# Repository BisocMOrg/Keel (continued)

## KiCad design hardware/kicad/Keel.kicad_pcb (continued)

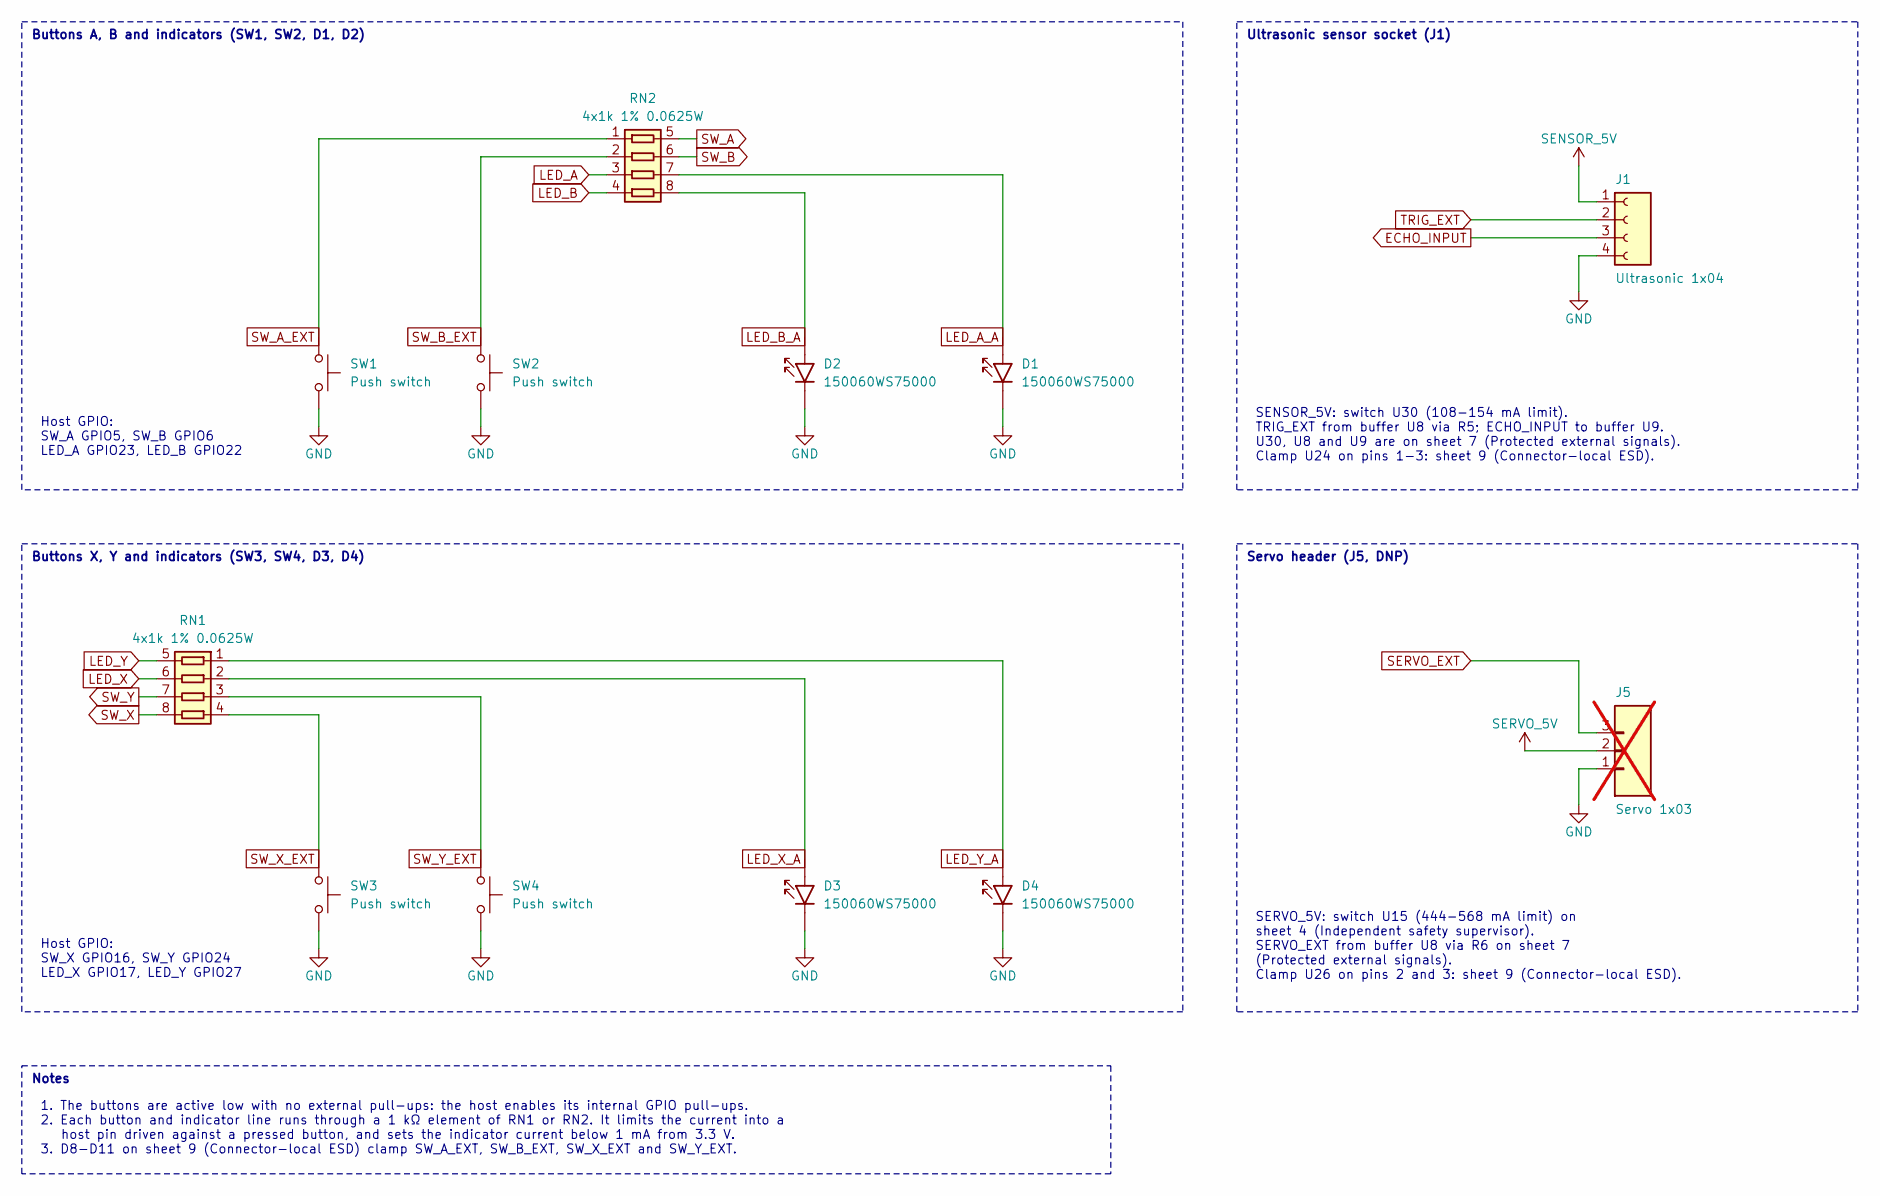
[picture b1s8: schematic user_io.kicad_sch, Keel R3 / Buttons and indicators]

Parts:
D1, D2, D3, D4: 150060WS75000; LED_0603_1608Metric; MPN 150060WS75000
J1: Ultrasonic 1x04; PinSocket_1x04_P2.54mm_Vertical; MPN SSW-104-01-G-S
J5: Servo 1x03; PinHeader_1x03_P2.54mm_Vertical; not fitted
RN1, RN2: 4x1k 1% 0.0625W; YC164_4x0603; MPN YC164-FR-071KL
SW1, SW2, SW3, SW4: Push switch; SW_SPST_PTS645Sx43SMTR92; MPN PTS645SM43SMTR92

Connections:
ECHO_INPUT: J1.3; also elsewhere on the board
GND: D1.1 (K), D2.1 (K), D3.1 (K), D4.1 (K), J1.4, J5.1, SW1.2 (ground), SW2.2 (ground), SW3.2 (ground), SW4.2 (ground); also elsewhere on the board
LED_A: RN2.3; also elsewhere on the board
LED_A_A: D1.2 (A), RN2.7
LED_B: RN2.4; also elsewhere on the board
LED_B_A: D2.2 (A), RN2.8
LED_X: RN1.6; also elsewhere on the board
LED_X_A: D3.2 (A), RN1.2
LED_Y: RN1.5; also elsewhere on the board
LED_Y_A: D4.2 (A), RN1.1
SENSOR_5V: J1.1; also elsewhere on the board
SERVO_5V: J5.2; also elsewhere on the board
SERVO_EXT: J5.3; also elsewhere on the board
SW_A: RN2.5; also elsewhere on the board
SW_A_EXT: RN2.1, SW1.1 (contact); also elsewhere on the board
SW_B: RN2.6; also elsewhere on the board
SW_B_EXT: RN2.2, SW2.1 (contact); also elsewhere on the board
SW_X: RN1.8; also elsewhere on the board
SW_X_EXT: RN1.4, SW3.1 (contact); also elsewhere on the board
SW_Y: RN1.7; also elsewhere on the board
SW_Y_EXT: RN1.3, SW4.1 (contact); also elsewhere on the board
TRIG_EXT: J1.2; also elsewhere on the board

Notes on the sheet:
Buttons A, B and indicators (SW1, SW2, D1, D2)
Buttons X, Y and indicators (SW3, SW4, D3, D4)
Ultrasonic sensor socket (J1)
Servo header (J5, DNP)
Host GPIO: SW_A GPIO5, SW_B GPIO6 LED_A GPIO23, LED_B GPIO22
Host GPIO: SW_X GPIO16, SW_Y GPIO24 LED_X GPIO17, LED_Y GPIO27
SENSOR_5V: switch U30 (108-154 mA limit). TRIG_EXT from buffer U8 via R5; ECHO_INPUT to buffer U9. U30, U8 and U9 are on sheet 7 (Protected external signals). Clamp U24 on pins 1-3: sheet 9 (Connector-local ESD).
SERVO_5V: switch U15 (444-568 mA limit) on sheet 4 (Independent safety supervisor). SERVO_EXT from buffer U8 via R6 on sheet 7 (Protected external signals). Clamp U26 on pins 2 and 3: sheet 9 (Connector-local ESD).
Notes
1. The buttons are active low with no external pull-ups: the host enables its internal GPIO pull-ups. 2. Each button and indicator line runs through a 1 kΩ element of RN1 or RN2. It limits the current into a host pin driven against a pressed button, and sets the indicator current below 1 mA from 3.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

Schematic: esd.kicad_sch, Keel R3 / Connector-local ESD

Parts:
D8, D9, D10, D11: TPD1E05U06DYAR; TI_DYA0002A_TPD1E05U06_SOD523; MPN TPD1E05U06DYAR
U17, U18, U19, U20, U21, U22, U23, U24, U25, U26: TPD4E05U06DQAR; TI_DQA0010A_TPD4E05U06_AB_Compatible_CommonMask; MPN TPD4E05U06DQAR

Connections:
ECHO_INPUT: U24.4 (IO4); also elsewhere on the board
EXP_3V3: U17.1 (IO1), U18.1 (IO1), U19.1 (IO1), U20.1 (IO1), U21.1 (IO1), U22.1 (IO1), U23.1 (IO1), U25.1 (IO1); also elsewhere on the board
EXP_I2C_SCL: U17.4 (IO4), U18.4 (IO4), U19.4 (IO4), U20.4 (IO4), U21.4 (IO4), U22.4 (IO4), U23.4 (IO4), U25.4 (IO4); also elsewhere on the board
EXP_I2C_SDA: U17.2 (IO2), U18.2 (IO2), U19.2 (IO2), U20.2 (IO2), U21.2 (IO2), U22.2 (IO2), U23.2 (IO2), U25.2 (IO2); also elsewhere on the board
EXP_INT_INPUT: U17.5 (IO5), U18.5 (IO5), U19.5 (IO5), U20.5 (IO5), U21.5 (IO5), U25.5 (IO5); also elsewhere on the board
GND: D8.2 (GND), D9.2 (GND), D10.2 (GND), D11.2 (GND), U17.3 (GND), U17.8 (GND), U18.3 (GND), U18.8 (GND), U19.3 (GND), U19.8 (GND), U20.3 (GND), U20.8 (GND), U21.3 (GND), U21.8 (GND), U22.3 (GND), U22.8 (GND), U23.3 (GND), U23.8 (GND), U24.3 (GND), U24.8 (GND), U25.3 (GND), U25.8 (GND), U26.3 (GND), U26.8 (GND); also elsewhere on the board
SENSOR_5V: U24.1 (IO1); also elsewhere on the board
SERVO_5V: U26.1 (IO1); also elsewhere on the board
SERVO_EXT: U26.2 (IO2); also elsewhere on the board
SW_A_EXT: D8.1 (IO1); also elsewhere on the board
SW_B_EXT: D9.1 (IO1); also elsewhere on the board
SW_X_EXT: D10.1 (IO1); also elsewhere on the board
SW_Y_EXT: D11.1 (IO1); also elsewhere on the board
TRIG_EXT: U24.2 (IO2); also elsewhere on the board

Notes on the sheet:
Protects JP1
Protects JP2
Protects JP3
Protects JP4
Protects JP5
Expansion header clamps (U17-U21)
Protects J4
Protects X1
Protects X3
J4 and I2C socket clamps (U25, U22, U23)
Protects J1
Ultrasonic sensor socket clamp (U24)
Protects J5
Servo header clamp (U26)
Protects SW1
Protects SW2
Protects SW3
Protects SW4
Push-button clamps (D8-D11)
Notes
1. Each clamp sits beside the connector or switch it protects, with a short, direct return to GND. 2. IO1 of each array clamps the connector supply pin (EXP_3V3, SENSOR_5V or SERVO_5V). 3. The clamps absorb ESD transients only. Sustained faults are handled downstream by the series resistors, curren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

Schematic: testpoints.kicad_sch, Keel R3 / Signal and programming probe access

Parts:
TP1: PI_5V; TestPoint_Pad_D1.5mm; MPN BARE PCB PAD - NO FITTED PART
TP2: SYS_5V; TestPoint_Pad_D1.5mm; MPN BARE PCB PAD - NO FITTED PART
TP3: VM_MOTOR; TestPoint_Pad_D1.5mm; MPN BARE PCB PAD - NO FITTED PART
TP4: PI_3V3; TestPoint_Pad_D1.5mm; MPN BARE PCB PAD - NO FITTED PART
TP5: EXP_3V3; TestPoint_Pad_D1.5mm; MPN BARE PCB PAD - NO FITTED PART
TP6, TP40: GND; TestPoint_Pad_D1.5mm; MPN BARE PCB PAD - NO FITTED PART
TP7: I2C_SDA; TestPoint_Pad_D1.5mm; MPN BARE PCB PAD - NO FITTED PART
TP8: I2C_SCL; TestPoint_Pad_D1.5mm; MPN BARE PCB PAD - NO FITTED PART
TP9: MOTOR_EN; TestPoint_Pad_D1.5mm; MPN BARE PCB PAD - NO FITTED PART
TP10: MOTOR_FAULT; TestPoint_Pad_D1.5mm; MPN BARE PCB PAD - NO FITTED PART
TP12: MOTOR_ISEN_A; TestPoint_Pad_D1.5mm; MPN BARE PCB PAD - NO FITTED PART
TP13: MOTOR_ISEN_B; TestPoint_Pad_D1.5mm; MPN BARE PCB PAD - NO FITTED PART
TP18: EXP_I2C_SDA; TestPoint_Pad_D1.5mm; MPN BARE PCB PAD - NO FITTED PART
TP19: EXP_I2C_SCL; TestPoint_Pad_D1.5mm; MPN BARE PCB PAD - NO FITTED PART
TP20: I2C_OVP_REF; TestPoint_Pad_D1.5mm; MPN BARE PCB PAD - NO FITTED PART
TP21: HOST_ARMED; TestPoint_Pad_D1.5mm; MPN BARE PCB PAD - NO FITTED PART
TP39: SAFE_3V3; TestPoint_Pad_D1.5mm; MPN BARE PCB PAD - NO FITTED PART
TP41: SAFETY_NRST; TestPoint_Pad_D1.5mm; MPN BARE PCB PAD - NO FITTED PART
TP42: SAFETY_SWDIO; TestPoint_Pad_D1.5mm; MPN BARE PCB PAD - NO FITTED PART
TP43: SAFETY_SWCLK; TestPoint_Pad_D1.5mm; MPN BARE PCB PAD - NO FITTED PART
TP44: MCU_WD_SERVICE; TestPoint_Pad_D1.5mm; MPN BARE PCB PAD - NO FITTED PART
TP45: SERVO_5V; TestPoint_Pad_D1.5mm; MPN BARE PCB PAD - NO FITTED PART
TP46: SERVO_POWER_EN; TestPoint_Pad_D1.5mm; MPN BARE PCB PAD - NO FITTED PART

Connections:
EXP_3V3: TP5.1 (1_1); also elsewhere on the board
EXP_I2C_SCL: TP19.1 (1_1); also elsewhere on the board
EXP_I2C_SDA: TP18.1 (1_1); also elsewhere on the board
GND: TP6.1 (1_1), TP40.1 (1_1); also elsewhere on the board
HOST_ARMED: TP21.1 (1_1); also elsewhere on the board
I2C_OVP_REF: TP20.1 (1_1); also elsewhere on the board
I2C_SCL: TP8.1 (1_1); also elsewhere on the board
I2C_SDA: TP7.1 (1_1); also elsewhere on the board
MCU_WD_SERVICE: TP44.1 (1_1); also elsewhere on the board
MOTOR_EN: TP9.1 (1_1); also elsewhere on the board
MOTOR_FAULT: TP10.1 (1_1); also elsewhere on the board
MOTOR_ISEN_A: TP12.1 (1_1); also elsewhere on the board
MOTOR_ISEN_B: TP13.1 (1_1); also elsewhere on the board
PI_3V3: TP4.1 (1_1); also elsewhere on the board
PI_5V: TP1.1 (1_1); also elsewhere on the board
SAFETY_NRST: TP41.1 (1_1); also elsewhere on the board
SAFETY_SWCLK: TP43.1 (1_1); also elsewhere on the board
SAFETY_SWDIO: TP42.1 (1_1); also elsewhere on the board
SAFE_3V3: TP39.1 (1_1); also elsewhere on the board
SERVO_5V: TP45.1 (1_1); also elsewhere on the board
SERVO_POWER_EN: TP46.1 (1_1); also elsewhere on the board
SYS_5V: TP2.1 (1_1); also elsewhere on the board
VM_MOTOR: TP3.1 (1_1); also elsewhere on the board

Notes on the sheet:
Pos
Net
Ref
Silkscreen
Expected reading
2 SYS5V
Within 60 mV of TP1 with U2 on; 0 V after a trip
6 GND
Row ground return
1 PI5V
5.0-5.1 V; below 5.2 V (U2 OVP trip 5.28 V min)
POWER row
13 ISB
Left motor shunt R36; chops at 180-230 mV
12 ISA
Right motor shunt R35; chops at 180-230 mV
GND
TP25
25 GND
Row ground return, sheet 11 (Local probe ground returns)
3 VM
TP2 minus the D5 drop (0.3-0.4 V while driving)
MOTOR row
45 S5V
5 V only during a servo burst (500 ms max)
TP47
47 GND
SERVO row
39 3V3S
3.234-3.366 V; probe VTref only, never feed
40 GND
41 RST
U12 NRST; held LOW while MOTOR_FAULT is LOW
43 CLK
SWD clock, U12 PA14-BOOT0
42 DIO
SWD data, U12 PA13
Set SW5 to PROG (all ON) before attaching an SWD probe.
SWD row
44 WDI

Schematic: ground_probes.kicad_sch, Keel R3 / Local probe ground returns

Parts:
TP24, TP25, TP26, TP47: GND; TestPoint_Pad_D1.5mm; MPN BARE PCB PAD - NO FITTED PART

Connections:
GND: TP24.1 (1_1), TP25.1 (1_1), TP26.1 (1_1), TP47.1 (1_1); also elsewhere on the board

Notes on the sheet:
Row
Pos
Net
Ref
Silkscreen
Ground return for
MOTOR
25 GND
TP13, TP12, TP3
SERVO
47 GND
TP45
STATUS
26 GND
TP44, TP4, TP10, TP21, TP9, TP46
I2C
24 GND
TP7, TP8, TP18, TP19, TP20, TP5
Row GND pads
Notes
1. Bare 1.5 mm ENIG pads on the bottom side, without paste or a fitted part; they are not in the BOM. 2. Each pad sits in its probe row on the 2.54 mm grid, beside the row signals, for a short return loop. 3. Pos counts along the row from its silkscreen label (west to east in top view), as on sheet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

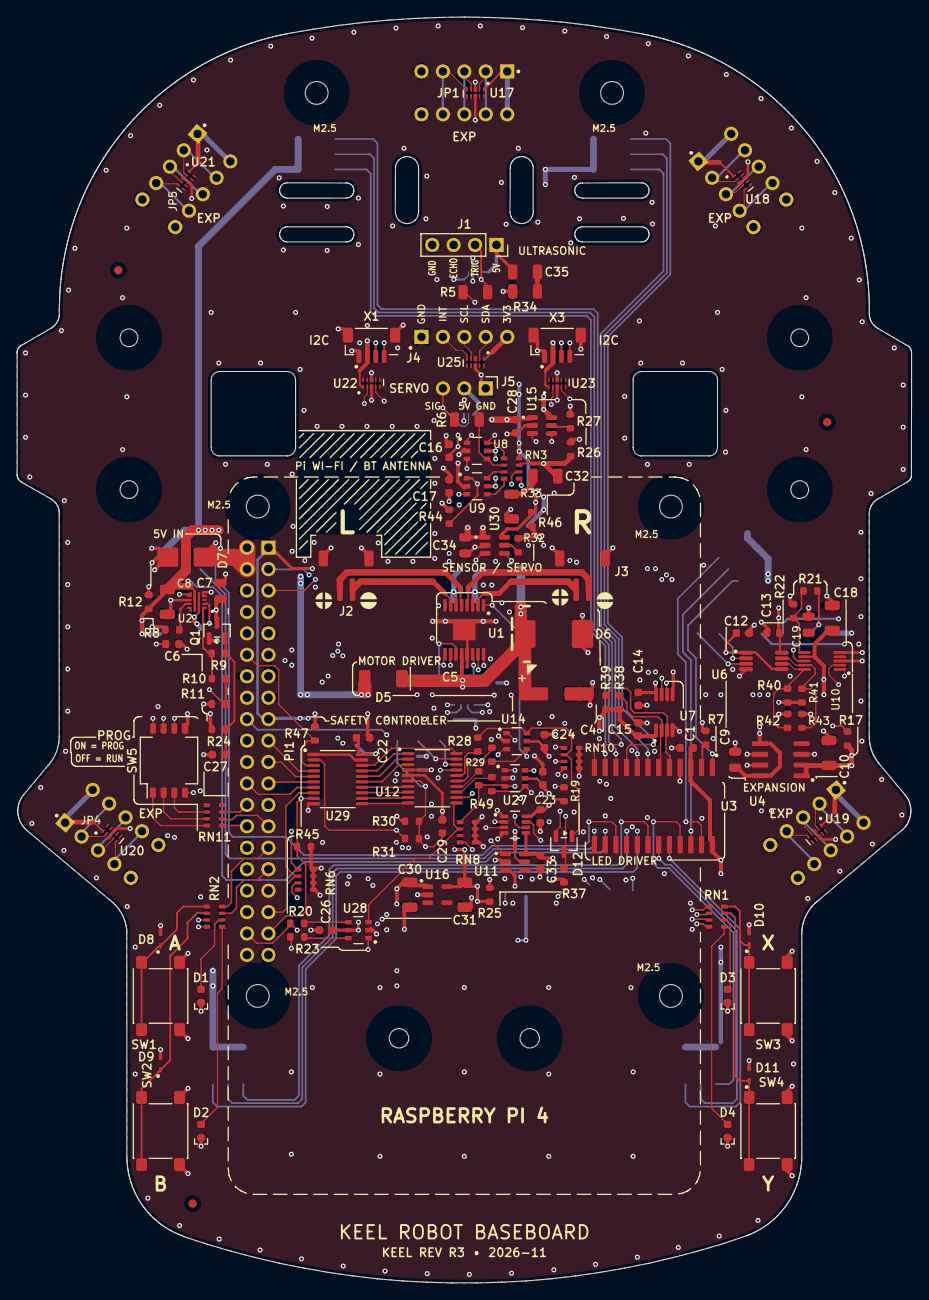
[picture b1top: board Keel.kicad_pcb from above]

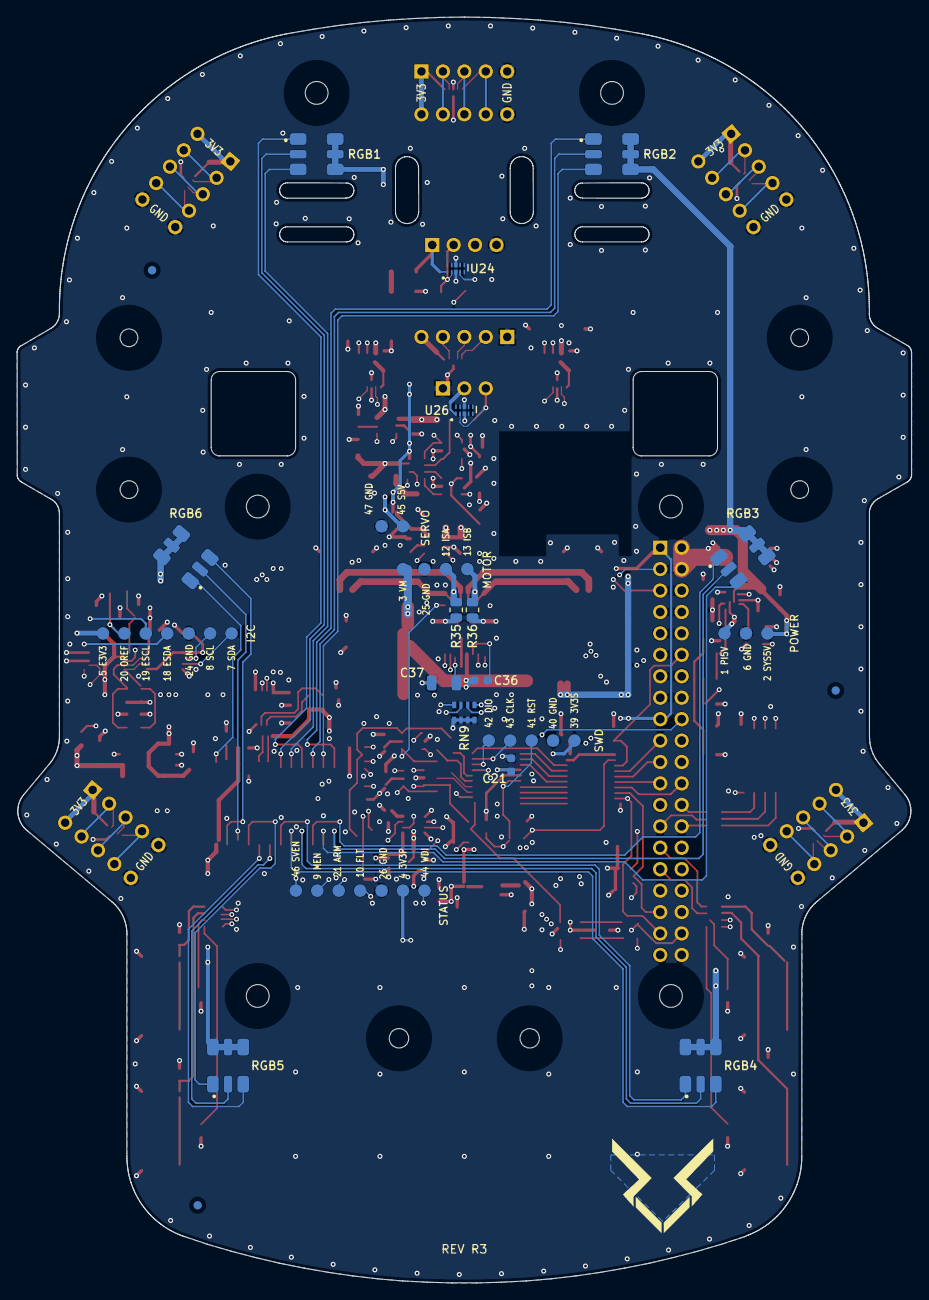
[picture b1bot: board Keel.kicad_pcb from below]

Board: 6 copper layers, 106.0 x 150.0 mm, 193 parts (45 on the bottom side), 124 nets.

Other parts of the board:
FID1, FID2, FID3, FID4, FID5, FID6: Fiducial; Fiducial_1mm_Mask2mm
H1, H2: MountingHole_2.3mm_NPTH
H3, H5: MountingHole_2.7mm_NPTH_PiHeaderClip
H4, H6, H11, H12: MountingHole_2.7mm_NPTH
H7, H8, H9, H10: MountingHole_2.1mm_NPTH

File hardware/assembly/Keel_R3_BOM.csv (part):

Item,Qty per board,Designators,Manufacturer,Manufacturer Part Number,Description,Value,Package,Mounting,Side,Approved alternates,Notes,Footprint (CPL)
1,1,PI1,Samtec,SSW-120-01-G-D,"Socket strip, female, 2x20, 2.54 mm pitch, vertical, through-hole, gold, lead style -01 (Raspberry Pi 40-pin)",2x20 female socket,"THT 2x20, 2.54 mm",THT,Top,,"exact part only - no substitution; THT, not in the CPL: hand-solder after reflow, no wave soldering (selective soldering only by prior agreement); seat flush and square; lead style -01 (tail length) required",PinSocket_2x20_P2.54mm_Vertical
2,1,U1,Texas Instruments,DRV8411PWPR,"Dual H-bridge motor driver, 1.65-11 V, current regulation on external sense resistors",DRV8411PWPR,HTSSOP-16 PowerPAD (PWP),SMD,Top,"DRV8833PWPR (TI) - the ONLY accepted alternate; C36/C37 are fitted for it. NOT DRV8411APWPR, NOT any DRV8833 ""-HX"" clone",exact part only - no substitution (the listed alternate / packaging variant is approved); exposed PowerPAD must be soldered; X-ray first boards,DRV8411A_PWP0016_C01_ExternalVias
3,1,C4,Panasonic,EEE-FP1C470AP,"Aluminium electrolytic capacitor, 47 uF, 16 V, low ESR, SMD (FP series)",47uF 16V,SMD Al-electrolytic 6.3 x 5.8 mm,SMD,Top,,POLARIZED: + terminal on pad 1 (VM_MOTOR); 5.8 mm tall,CP_Elec_6.3x5.8
4,2,"J2,J3",JST,S2B-ZR-SM4A-TF(LF)(SN),"Connector header, JST ZH, 2-pos, 1.5 mm pitch, side entry, SMD, tin",JST ZH 2-pin,"SMD, 1x02 + 2 MP",SMD,Top,,engineering BOM code S2B-ZR-SM4A-TF,JST_ZH_S2B-ZR-SM4A-TF_1x02-1MP_P1.50mm_Horizontal
5,1,U3,Lumissil,IS31FL3218-GRLS2,"18-channel constant-current LED driver, I2C",IS31FL3218-GRLS2,SOP-24,SMD,Top,"IS31FL3218-GRLS2-TR (same part, tape and reel)",exact part only - no substitution (the listed alternate / packaging variant is approved),IS31FL3218_SOP24
6,16,"C1,C12,C13,C14,C15,C16,C17,C21,C22,C23,C24,C25,C26,C27,C28,C33",Murata,GRM188R72A104KA35D,"MLCC 100 nF, 100 V, X7R, +/-10%",100nF 100V X7R,0603 (1608 metric),SMD,Both,"packaging suffix only (Murata D<->J paper reel, L<->K embossed reel)","top: C1,C12,C13,C14,C15,C16,C17,C22,C23,C24,C25,C26,C27,C28,C33; bottom: C21",C_0603_1608Metric
7,1,R7,YAGEO,RC0603FR-0712KL,"Thick-film resistor 12 kohm, 1%, 0.1 W",12k 1%,0603 (1608 metric),SMD,Top,,,R_0603_1608Metric
8,6,"RGB1,RGB2,RGB3,RGB4,RGB5,RGB6",Inolux,IN-P55TATRGB,"RGB LED, top-view, 3 chips (R/G/B), PLCC-6",RGB LED,PLCC-6 5.0 x 5.5 mm,SMD,Bottom,,"BOTTOM side (top-view LED mounted on B, emits away from the board); pin 1 = silk dot / chamfered corner on sheet 2 of Keel_R3_assembly_drawing.pdf (pad 1 = blue cathode, pads 4-6 common anode); bottom CPL angles are KiCad-native (X not mirrored), so orient by that sheet",LED_Inolux_IN-P55TATRGB_PLCC6_5.0x5.5mm_P1.8mm
9,2,"X1,X3",JST,BM04B-SRSS-TB(LF)(SN),"Connector header, JST SH, 4-pos, 1.0 mm pitch, vertical (top entry), SMD, tin",I2C JST-SH 4P,"SMD, 1x04 + 2 MP",SMD,Top,,engineering BOM code BM04B-SRSS-TB,JST_SH_BM04B-SRSS-TB_1x04-1MP_P1.00mm_Vertical
10,1,J1,Samtec,SSW-104-01-G-S,"Socket strip, female, 1x4, 2.54 mm pitch, vertical, through-hole, gold, lead style -01 (HC-SR04)",1x4 female socket,"THT 1x4, 2.54 mm",THT,Top,,"exact part only - no substitution; THT, not in the CPL: hand-solder after reflow, no wave soldering (selective soldering only by prior agreement); seat flush and square",PinSocket_1x04_P2.54mm_Vertical
11,2,"R5,R6",YAGEO,RC1206FR-07330RL,"Thick-film resistor 330 ohm, 1%, 0.25 W",330R 1%,1206 (3216 metric),SMD,Top,,,R_1206_3216Metric
12,4,"RN1,RN2,RN3,RN11",YAGEO,YC164-FR-071KL,"Resistor array, 4 x 1 kohm, 1%, isolated, convex terminals",4x 1k 1%,YC164 array 3.2 x 1.6 mm (4x0603),SMD,Top,,,YC164_4x0603
13,4,"D1,D2,D3,D4",Wurth Elektronik,150060WS75000,"LED, white, 0603, water-clear, max. height 0.5 mm",LED white,0603 (1608 metric),SMD,Top,,"POLARITY: the body mark is the ANODE -> PCB pad 2 (LED_x_A), away from the silk cathode bracket; CPL angle already includes +180 deg",LED_0603_1608Metric
14,4,"SW1,SW2,SW3,SW4",C&K,PTS645SM43SMTR92 LFS,"Tactile switch, SPST-NO, 6 x 6 mm, 4.3 mm height, SMD gull-wing",Tactile switch,SMD 6 x 6 mm,SMD,Top,,engineering BOM code PTS645SM43SMTR92,SW_SPST_PTS645Sx43SMTR92
15,1,C5,Murata,GRM033R61E104KE14D,"MLCC 100 nF, 25 V, X5R, +/-10%",100nF 25V X5R,0201 (0603 metric),SMD,Top,"packaging suffix only (Murata D<->J paper reel, L<->K embossed reel)",0201 placed beside U1,C_0201_0603Metric
16,1,D5,Nexperia,PMEG6030ELPX,"Schottky rectifier, 60 V, 3 A",PMEG6030ELPX,SOD-128,SMD,Top,,"engineering BOM code PMEG6030ELP,115; POLARIZED: cathode band on pad 1 (VM_MOTOR)",D_SOD-128
17,1,D6,STMicroelectronics,SM15T6V8A,"TVS diode, UNIDIRECTIONAL, 1500 W, 5.8 V stand-off / 6.8 V breakdown",SM15T6V8A,SMC (DO-214AB),SMD,Top,,engineering BOM code SM15T6V8A-TR; UNIDIRECTIONAL (not SM15T6V8CA); cathode band on pad 1 (VM_MOTOR),D_SMC
18,7,"R12,R20,R23,R26,R28,R29,R31",YAGEO,RC0603FR-071KL,"Thick-film resistor 1 kohm, 1%, 0.1 W",1k 1%,0603 (1608 metric),SMD,Top,,,R_0603_1608Metric
19,1,U2,Texas Instruments,TPS259474LRPWR,"eFuse / protected load switch, 2.7-23 V, 5.5 A, adjustable UV/OV/ILIM",TPS259474LRPWR,VQFN-HR-10 (RPW) 2 x 2 mm,SMD,Top,,exact part only - no substitution; leadless VQFN-HR; X-ray first boards,TPS25947_RPW0010A
20,1,U4,Analog Devices,LT1763IS8-3.3#PBF,"LDO regulator, 3.3 V fixed, 500 mA, low noise",LT1763-3.3,SOIC-8,SMD,Top,"LT1763IS8-3.3#TRPBF (same part, tape and reel)",,SOIC-8_3.9x4.9mm_P1.27mm
21,1,R8,YAGEO,RC0603FR-072K21L,"Thick-film resistor 2.21 kohm, 1%, 0.1 W",2.21k 1%,0603 (1608 metric),SMD,Top,,,R_0603_1608Metric
22,1,R9,Panasonic,ERA-3ARB3162V,"Thin-film resistor 31.6 kohm, 0.1%, 10 ppm/C, 0.1 W",31.6k 0.1%,0603 (1608 metric),SMD,Top,,,R_0603_1608Metric
23,1,R10,Panasonic,ERA-3ARB3091V,"Thin-film resistor 3.09 kohm, 0.1%, 10 ppm/C, 0.1 W",3.09k 0.1%,0603 (1608 metric),SMD,Top,,,R_0603_1608Metric
24,1,R11,YAGEO,RT0603BRB0710KL,"Thin-film resistor 10 kohm, 0.1%, 10 ppm/C, 0.1 W",10k 0.1%,0603 (1608 metric),SMD,Top,,,R_0603_1608Metric
25,1,C6,Murata,GRM1885C1H472JA01D,"MLCC 4.7 nF, 50 V, C0G, +/-5%",4.7nF 50V C0G,0603 (1608 metric),SMD,Top,"packaging suffix only (Murata D<->J paper reel, L<->K embossed reel)",,C_0603_1608Metric
26,4,"C7,C9,C19,C34",Murata,GRM219R71E105KA88D,"MLCC 1 uF, 25 V, X7R, +/-10%",1uF 25V X7R,0805 (2012 metric),SMD,Top,"packaging suffix only (Murata D<->J paper reel, L<->K embossed reel)",,C_0805_2012Metric
27,3,"C8,C10,C32",Murata,GRM31CR71E106KA12L,"MLCC 10 uF, 25 V, X7R, +/-10%",10uF 25V X7R,1206 (3216 metric),SMD,Top,"packaging suffix only (Murata D<->J paper reel, L<->K embossed reel)",,C_1206_3216Metric
28,1,U11,Texas Instruments,TPS3808G50DBVT,"Voltage supervisor, 4.65 V threshold, adjustable delay",TPS3808G50DBVT,SOT-23-6,SMD,Top,,exact part only - no substitution,SOT-23-6
29,4,"RN6,RN8,RN9,RN10",YAGEO,YC164-FR-0710KL,"Resistor array, 4 x 10 kohm, 1%, isolated, convex terminals",4x 10k 1%,YC164 array 3.2 x 1.6 mm (4x0603),SMD,Both,,"top: RN6,RN8,RN10; bottom: RN9",YC164_4x0603
30,2,"U6,U7",Texas Instruments,TCA9517ADGKR,Level-translating I2C bus repeater,TCA9517ADGKR,VSSOP-8 (DGK),SMD,Top,,exact part only - no substitution,VSSOP-8_3x3mm_P0.65mm
31,1,U8,Nexperia,"74LVC2G07GV,125","Dual buffer, open-drain outputs, 5.5 V tolerant",74LVC2G07GV,"SOT457 (SC-74, 6-pin)",SMD,Top,"74LVC2G07GV-Q100H (Nexperia, same pinout). NOT non-Nexperia ""74LVC2G07GV"" listings",,Nexperia_SOT457_SC74_1.5x2.9mm_P0.95mm
32,2,"U9,U28",Nexperia,"74LVC2G17GV,125",Dual non-inverting Schmitt-trigger buffer,74LVC2G17GV,"SOT457 (SC-74, 6-pin)",SMD,Top,,,Nexperia_SOT457_SC74_1.5x2.9mm_P0.95mm
33,5,"R17,R46,R47,R48,R49",YAGEO,RC0603FR-0710KL,"Thick-film resistor 10 kohm, 1%, 0.1 W",10k 1%,0603 (1608 metric),SMD,Top,,,R_0603_1608Metric
34,5,"R19,R42,R43,R44,R45",YAGEO,RC0603FR-0722KL,"Thick-film resistor 22 kohm, 1%, 0.1 W",22k 1%,0603 (1608 metric),SMD,Top,,,R_0603_1608Metric
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
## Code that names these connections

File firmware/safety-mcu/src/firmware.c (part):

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__attribute__((section(".noinit"))) static volatile sensor_guard guard_slot[2];
static sensor_guard guard; /* this boot's working copy */
static uint32_t guard_at;
#define MOTOR_PIN (1u<<11) /* PA11 pin16 MCU_MOTOR_PERMIT_RAW */
#define SERVO_PIN (1u<<7) /* PA7 pin14 MCU_SERVO_PERMIT_RAW */
#define SENSOR_PIN (1u<<12) /* PA12 pin17 SENSOR_POWER_EN */
#define READY_PIN (1u<<4) /* PA4 pin11 MCU_READY */
#define WDI_PIN (1u<<5) /* PA5 pin12 MCU_WD_SERVICE */
#define PWM_EXTI ((1u<<0)|(1u<<1)|(1u<<14)|(1u<<15)) /* PA0 LN, PA1 LP, PC14 RP, PC15 RN */
#define FAULT_EXTI (1u<<6) /* PB6 pin20 SENSE_MOTOR_FAULT */
#define CONTROL_EXTI ((1u<<3)|(1u<<7)) /* PA3 SENSE_MOTOR_EN, PB7 SENSE_HOST_HEARTBEAT */
#define OUTPUT_PINS (MOTOR_PIN|SERVO_PIN|SENSOR_PIN|READY_PIN|WDI_PIN) /* all GPIOA */
/* firmware_diagnostic (SWD-readable): bits 0-10 controller.last_faults, bits 16-17
 * sensor strikes, bit 31 sensor strike lockout. 0x48415244 marks a HardFault. */
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static void exti_events(void) {
 uint32_t rising=EXTI->RPR1&(PWM_EXTI|FAULT_EXTI|CONTROL_EXTI);
 uint32_t falling=EXTI->FPR1&(PWM_EXTI|FAULT_EXTI|CONTROL_EXTI);
 if((rising|falling)&(1u<<3))enable_edge_count+=((rising>>3)&1u)+((falling>>3)&1u); /* PA3 */
 if(falling&(1u<<7))hb_fall_count++; /* PB7 */
 pwm_activity|=(rising|falling)&PWM_EXTI;
 if(falling&FAULT_EXTI) {
  fault_edge=1;
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 for(unsigned n=0;n<=12;n++)pin_mode(GPIOA,n,0);
 pin_mode(GPIOB,6,0);pin_mode(GPIOB,7,0);pin_mode(GPIOC,14,0);pin_mode(GPIOC,15,0);
 for(unsigned n=0;n<=12;n++)if(OUTPUT_PINS&(1u<<n))pin_mode(GPIOA,n,1);
 /* PA13/PA14 remain SWD. PF2/NRST is never repurposed. */
 EXTI->EXTICR[0]&=~((7u<<0)|(7u<<8)|(7u<<24)); /* PA0/PA1/PA3 */
 EXTI->EXTICR[1]=(EXTI->EXTICR[1]&~((7u<<16)|(7u<<24)))|(1u<<16)|(1u<<24); /* PB6,PB7 (PA6/PA7 not routed) */
 EXTI->EXTICR[3]=(EXTI->EXTICR[3]&~((7u<<16)|(7u<<24)))|(2u<<16)|(2u<<24); /* PC14,PC15 */
 EXTI->RTSR1|=PWM_EXTI|(1u<<3);EXTI->FTSR1|=PWM_EXTI|FAULT_EXTI|CONTROL_EXTI;
 EXTI->RPR1=PWM_EXTI|FAULT_EXTI|CONTROL_EXTI;EXTI->FPR1=PWM_EXTI|FAULT_EXTI|CONTROL_EXTI;
 EXTI->IMR1|=PWM_EXTI|FAULT_EXTI|CONTROL_EXTI;
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 i.heartbeat_event_mode=true;
 enable_edge_count=0;hb_fall_count=0;
 __enable_irq();
 i.enable=(a&(1u<<3))!=0;i.heartbeat=(b&(1u<<7))!=0;i.servo_request=(a&(1u<<2))!=0; /* PA3,PB7,PA2 */
 i.hardware_fault_high=(b&(1u<<6))!=0; /* PB6 */
 i.pwm_levels=((c>>15)&1u)|(((c>>14)&1u)<<1)|(((a>>0)&1u)<<2)|(((a>>1)&1u)<<3); /* RN PC15,RP PC14,LN PA0,LP PA1 */
 i.motor_feedback=(a&(1u<<8))!=0;i.servo_feedback=(a&(1u<<6))!=0; /* PA8,PA6 */
 i.host_rail_ok=supply_ok; /* core ABI name retained; this revision monitors SAFE rail only */
 i.internal_ok=internal_ok;return i;
}
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}
static void apply(safety_output o) {
 __disable_irq();
 if(fault_edge || !(GPIOB->IDR&(1u<<6)))o.motor_permit=o.servo_permit=o.sensor_permit=o.ready=false; /* PB6 fault bus */
 uint32_t set=(o.motor_permit?MOTOR_PIN:0)|(o.servo_permit?SERVO_PIN:0)|
  (o.sensor_permit?SENSOR_PIN:0)|(o.ready?READY_PIN:0)|(o.watchdog_level?WDI_PIN:0);
 /* One atomic BSRR write prevents sequential motor/servo transition overlap. */
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  i.sensor_strike_lockout=sensor_guard_lockout(&guard); /* re-read every pass */
  const enum safety_stage stage_before=controller.stage;
  safety_output o=safety_step(&controller,&i);
  /* The core already applies the lockout. PA12 also waits for this boot's first WDI
   * kick, so an external-watchdog reset left over from before this boot cannot
   * land inside the strike window of a switch-on. */
  o.sensor_permit=o.sensor_permit && !i.sensor_strike_lockout && wd_kicked;
  /* Record PA12 and any new F_EXTERNAL/F_RAIL latch before driving PA12 (apply can
   * only lower it): a reset caused by this switch-on always finds it in the record. */
  sensor_guard_tick(&guard,o.sensor_permit,i.now_ms-guard_at,
   sensor_guard_trip(stage_before,&controller));
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
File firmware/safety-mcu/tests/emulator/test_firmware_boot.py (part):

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the next boot still counts the switch-on once.
Main-loop cases continue into the foreground loop. Time advances only at the
WFI instruction: there the harness updates the modelled inputs, runs the real
EXTI handlers for heartbeat/GPIO26/PWM/fault edges and SysTick_Handler, then
resumes. After every EXTI6 fault edge the handler itself must already have
driven PA12, READY, motor and servo LOW. Every pass is checked for: both slots
rewritten (slot 0 then slot 1, equal and valid), then exactly one BSRR write
whose PA12 bit equals the record, so a PA12 rise is always recorded
(sensor_high=1, rise_age=0) before the BSRR write that drives it. The only
exception is a pass whose FAULT edge is injected between snapshot() and apply()
(at the safety_step call): there the record may say 1 but PA12 must stay LOW.
Scenarios: locked record (PA12 never set; READY, motor arming after an ACK and a
servo burst unaffected), unlocked record (PA12 after two heartbeat falls and the
first WDI kick), a U30 FAULT caught by EXTI6 or a SAFE3 sag without reset (three
strikes, then lockout), a FAULT edge between snapshot() and apply(), F_HEARTBEAT
and F_PWM latches soon after a switch-on (no strike), a fault bus LOW read only by
apply() (edge arriving while its interrupts are masked: that pass's output write must
already drop PA12, READY, motor and servo), a FAULT 51 ms after each
switch-on (the documented uncounted limit), and an in-boot strike followed by a
pin reset of the same event, including one that tears the strike pass's record
store (counted once).
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its EXTI line with EXTICR routed to its port, the edges and mask, no other line
unmasked, the EXTI IRQ groups enabled, SWD/GPIOF untouched and outputs LOW. A
main-loop case drives each edge line and each level input from the first ACK stage
and checks that the core latches the matching fault (GPIO26 double edge F_ACK, a
PWM edge or level on each of PA0/PA1/PC14/PC15 F_PWM, fault bus LOW on PB6
F_EXTERNAL) with READY dropped, and that nothing latches without a stimulus.
This runner builds nothing; --elf names another built image to check.
Results go to build/firmware_boot_tests.json (next to the image given with --elf),
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RAM_PARITY_CHECK=1<<22;NRST_MODE=3<<27
OPTR_OK=NRST_MODE|RAM_PARITY_CHECK|0xAA   # parity checking disabled (bit=1), bidirectional NRST, RDP level 0
OPTR_PARITY_ON=OPTR_OK&~RAM_PARITY_CHECK
# U12 outputs (all GPIOA): PA4 READY, PA5 WDI, PA7 servo permit, PA11 motor permit, PA12 sensor enable
PA4,PA5,PA7,PA11,PA12=1<<4,1<<5,1<<7,1<<11,1<<12
# U12 pin map (hardware/kicad/Keel.kicad_sch, part U12): (pin, port, bit, net, kind). kind: out = push-pull
# output; level = input without EXTI; fall/both = input alone on EXTI line <bit>, falling / both edges.
PIN_MAP=[(1,'B',7,'SENSE_HOST_HEARTBEAT','fall'),(2,'C',14,'SENSE_MOTOR_RP','both'),(3,'C',15,'SENSE_MOTOR_RN','both'),
 (7,'A',0,'SENSE_MOTOR_LN','both'),(8,'A',1,'SENSE_MOTOR_LP','both'),(9,'A',2,'SENSE_SERVO_REQUEST','level'),
 (10,'A',3,'SENSE_MOTOR_EN','both'),(11,'A',4,'MCU_READY','out'),(12,'A',5,'MCU_WD_SERVICE','out'),
 (13,'A',6,'SERVO_POWER_EN_FB','level'),(14,'A',7,'MCU_SERVO_PERMIT_RAW','out'),(15,'A',8,'MOTOR_EN_SAFE_FB','level'),
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
  self.in_loop=False;self.tick_reads=0;self.stop_at_rmvf=False;self.at_wfi=False;self.rmvf=False
  self.isr_errors=[];self.midpass_passes=set();self.midpass_armed=False;self.midpass_stop=False
  self.apply_fault_pass=None;self.idr_b_reads=0 # pass whose second GPIOB IDR read (apply()) sees PB6 LOW
  slot=img.slot;tick=s['tick_ms']
  def w32(a,v):u.mem_write(a,struct.pack('<I',v&0xffffffff))
  def r32(a):return struct.unpack('<I',bytes(u.mem_read(a,4)))[0]
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  for r,v in zip(regs,saved):u.reg_write(r,v)
  self.phase=phase
 def fault_isr(self):
  """EXTI6 FAULT edge: the real handler must itself drive PA12, READY, motor and servo LOW."""
  self.call('EXTI4_15_IRQHandler')
  if self.odr&(PA12|PA4|PA11|PA7):self.isr_errors.append('t=%d: EXTI6 handler left outputs %#x HIGH'%(self.t,self.odr&(PA12|PA4|PA11|PA7)))
 def step(self,world):
  """At WFI: advance 1 ms (inputs, EXTI handlers, SysTick), then run the next pass to WFI.
  If the world asks for it, a FAULT edge is delivered inside the pass, at the safety_step call
  (snapshot() already taken, apply() not yet run)."""
  self.t+=1;events=world.inputs(self,self.t)
  if events&((1<<0)|(1<<1)):self.call('EXTI0_1_IRQHandler') # PA0/PA1 PWM
  if events&((1<<2)|(1<<3)):self.call('EXTI2_3_IRQHandler') # PA3 GPIO26 enable
  if events&((1<<7)|(1<<14)|(1<<15)):self.call('EXTI4_15_IRQHandler') # PB7 heartbeat, PC14/PC15 PWM
  if events&(1<<6):self.fault_isr() # PB6 fault
  self.call('SysTick_Handler')
  self.pass_no+=1;self.at_wfi=False;before=self.odr;self.idr_b_reads=0
  self.midpass_armed=world.midpass_due(self,self.t);self.midpass_stop=False
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  world.after_pass(self,self.t,before,self.odr)

class World:
 """Pi and board model. hb: heartbeat falling-edge period/phase (ms). en(t): GPIO26.
 srv(t): servo request (PA2). fault: None, 'u30' (FAULT caught by EXTI6 fault_ms after
 each PA12 rise, no reset; with midpass=True the edge arrives inside that pass, between
 snapshot() and apply()) or 'sag' (SAFE3 reads 3.0 V on the pass after each PA12 rise).
 rise_events: one (kind, delay_ms) per PA12 rise, in order: 'hb' = an extra heartbeat
 fall (too early: F_HEARTBEAT), 'pwm' = a motor PWM edge on PA1 (F_PWM in an ACK stage)."""
 def __init__(self,hb_period=50,hb_phase=10,en=lambda t:False,srv=lambda t:False,fault=None,fault_ms=7,
              midpass=False,rise_events=()):
  self.hb_period=hb_period;self.hb_phase=hb_phase;self.en=en;self.srv=srv;self.fault=fault;self.fault_ms=fault_ms
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  if en!=self.last_en:
   if en:m.rpr|=1<<3
   else:m.fpr|=1<<3
   ev|=1<<3;self.last_en=en # PA3 = EXTI3
  hb_level=(t%self.hb_period)==(self.hb_phase-1)%self.hb_period
  if t%self.hb_period==self.hb_phase%self.hb_period:m.fpr|=1<<7;ev|=1<<7;self.falls.append(t) # PB7 = EXTI7
  kind=self.sched.pop(t,None)
  if kind=='hb':m.fpr|=1<<7;ev|=1<<7;self.fired.append(t)
  elif kind=='pwm':m.rpr|=1<<1;m.fpr|=1<<1;ev|=1<<1;self.fired.append(t) # short pulse: PA1 back LOW by the pass
  if self.fault=='u30' and not self.fault_midpass and self.fault_at==t and m.odr&PA12:
   m.fpr|=1<<6;ev|=1<<6;self.faults.append(t) # short FAULT pulse: EXTI6 latched, bus back HIGH before the next pass
  m.adc_raw=1600 if (self.fault=='sag' and self.sag_at==t) else 1455
  if self.fault=='sag' and self.sag_at==t:self.faults.append(t)
  fb_ok=en and bool(m.idr_b&(1<<6)) # PB6 fault bus
  # PA3 enable, PA2 servo request, PA8 MOTOR_EN_SAFE, PA6 SERVO_POWER_EN; PB6 fault bus HIGH, PB7 heartbeat
  m.idr_a=(int(en)<<3)|(int(bool(self.srv(t)))<<2)|(int(fb_ok and bool(m.odr&PA11))<<8)|(int(fb_ok and bool(m.odr&PA7))<<6)
  m.idr_b=(1<<6)|(int(hb_level)<<7);m.idr_c=0
  return ev
 def midpass_due(self,m,t):return self.fault=='u30' and self.fault_midpass and self.fault_at==t and bool(m.odr&PA12)
 def midpass(self,m,t):m.fpr|=1<<6;self.faults.append(t) # same short FAULT pulse, arriving inside the pass
 def after_pass(self,m,t,before,after):
  self.odr_log.append((t,after))
  if t in self.fired:self.diag_at[t]=m.var('firmware_diagnostic')
  if after&PA12 and not before&PA12:
   self.rises.append(t);self.fault_at=t+self.fault_ms;self.sag_at=t+1
   if self.rise_events:kind,delay=self.rise_events.pop(0);self.sched[t+delay]=kind
  if before&PA5 and not after&PA5:self.kicks.append(t)

def passes(m):
 """Group loop-phase log entries by pass number."""
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  if e[-2]=='loop':out.setdefault(e[-1],[]).append(e)
 return out
def pass_invariants(m):
 """Per pass: slot0 then slot1 fully rewritten (valid, equal), then one BSRR write whose PA12
 bit equals the stored sensor_high (on a pass with a FAULT edge injected before apply(), PA12
 must be LOW whatever the record says). Returns (errors, number of passes checked)."""
 err=[];n=0
 for k,ev in sorted(passes(m).items()):
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  if len(bs)!=1:err.append('pass %d has %d BSRR writes'%(k,len(bs)));continue
  last_w=max(j for j,e in enumerate(ev) if e[0]=='W')
  if bs[0]<last_w:err.append('pass %d BSRR before the record store'%k)
  pa12=(ev[bs[0]][1]>>12)&1
  if k in m.midpass_passes:
   if pa12:err.append('pass %d: apply() drove PA12 HIGH after a FAULT edge'%k)
  elif pa12!=s0[3]:err.append('pass %d PA12=%d but record sensor_high=%d'%(k,pa12,s0[3]))
  if len(err)>5:break
 return err,n
def rise_records(m):
 """For each pass whose BSRR write turns PA12 on: the record stored before it in that pass."""
 out=[];prev=0
 for k,ev in sorted(passes(m).items()):
  for j,e in enumerate(ev):
   if e[0]=='BSRR':
    now=(prev&~(e[1]>>16))|(e[1]&0xffff)
    if now&PA12 and not prev&PA12:
     ws=[x for x in ev[:j] if x[0]=='W']
     out.append((k,[x[2] for x in ws[:5]],[x[2] for x in ws[5:10]]))
    prev=now
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 if extra:err.append('EXTI lines unmasked without an edge input: %#x'%extra)
 for n in (13,14):
  if (moder['A']>>2*n)&3!=2 or (pupdr['A']>>2*n)&3!=(GPIO_RESET['A'][1]>>2*n)&3:err.append('PA%d (SWD) reconfigured'%n)
 if moder['F']!=GPIO_RESET['F'][0] or pupdr['F']!=GPIO_RESET['F'][1]:err.append('GPIOF (PF2/NRST) reconfigured')
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
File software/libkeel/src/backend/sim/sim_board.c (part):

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enum {
    PIN_LP = 8, PIN_RN = 9, PIN_RP = 10, PIN_LN = 11,
    PIN_BUTTON_A = 5, PIN_BUTTON_B = 6, PIN_BUTTON_X = 16, PIN_BUTTON_Y = 24,
    PIN_LED_A = 23, PIN_LED_B = 22, PIN_LED_X = 17, PIN_LED_Y = 27,
    PIN_HEARTBEAT = 18, PIN_SERVO_REQUEST = 19, PIN_READY = 20, PIN_ARMED = 21,
    PIN_ECHO = 25, PIN_ENABLE = 26
};

static const uint8_t button_pins[KEEL_BUTTON_COUNT] = {PIN_BUTTON_A, PIN_BUTTON_B, PIN_BUTTON_X,
                                                       PIN_BUTTON_Y};
static const uint8_t button_led_pins[KEEL_BUTTON_COUNT] = {PIN_LED_A, PIN_LED_B, PIN_LED_X,
                                                           PIN_LED_Y};

/* Serial-number comparison: epochs may wrap. */
static int epoch_older(uint32_t epoch, uint32_t newest)
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static void servo_off(keel__sim_board *b)
{
    b->servo_pulse_us = 0;
    b->servo_request = 0;
}

/* Counts the edges the MCU sees (it latches F_ACK on two ENABLE edges
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    input.now_ms = mcu_now_ms(b);
    input.enable = (b->outputs & KEEL_OUT_ENABLE) != 0;
    input.heartbeat = (b->outputs & KEEL_OUT_HEARTBEAT) != 0;
    input.servo_request = b->servo_request != 0;
    input.hardware_fault_high = !b->fault_low;
    input.hardware_fault_edge = b->fault_edge != 0;
    input.host_rail_ok = true;
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            b->now_us - b->coast_since_us < KEEL__BOARD_SERVO_IDLE_US) {
            return keel__board_latch(b, KEEL_E_INTERNAL, KEEL_CAUSE_INTERLOCK, 0, command->mode);
        }
        b->servo_request = 1;
        b->servo_until_us = command->valid_until_us;
    } else if (command->valid_until_us < b->servo_until_us) {
        b->servo_until_us = command->valid_until_us; /* shortened, never extended */
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                pin(PIN_LN, (b->levels & KEEL__PWM_LN) != 0) |
                pin(PIN_RP, (b->levels & KEEL__PWM_RP) != 0) |
                pin(PIN_RN, (b->levels & KEEL__PWM_RN) != 0) | pin(PIN_READY, b->permit.ready) |
                pin(PIN_ARMED, armed) | pin(PIN_SERVO_REQUEST, b->servo_request) |
                pin(PIN_ECHO, b->echo_phase == KEEL__ECHO_HIGH);
    for (i = 0; i < KEEL_BUTTON_COUNT; ++i) {
        out->pins |= pin(button_pins[i], !(b->buttons & (1u << i))); /* active low */
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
